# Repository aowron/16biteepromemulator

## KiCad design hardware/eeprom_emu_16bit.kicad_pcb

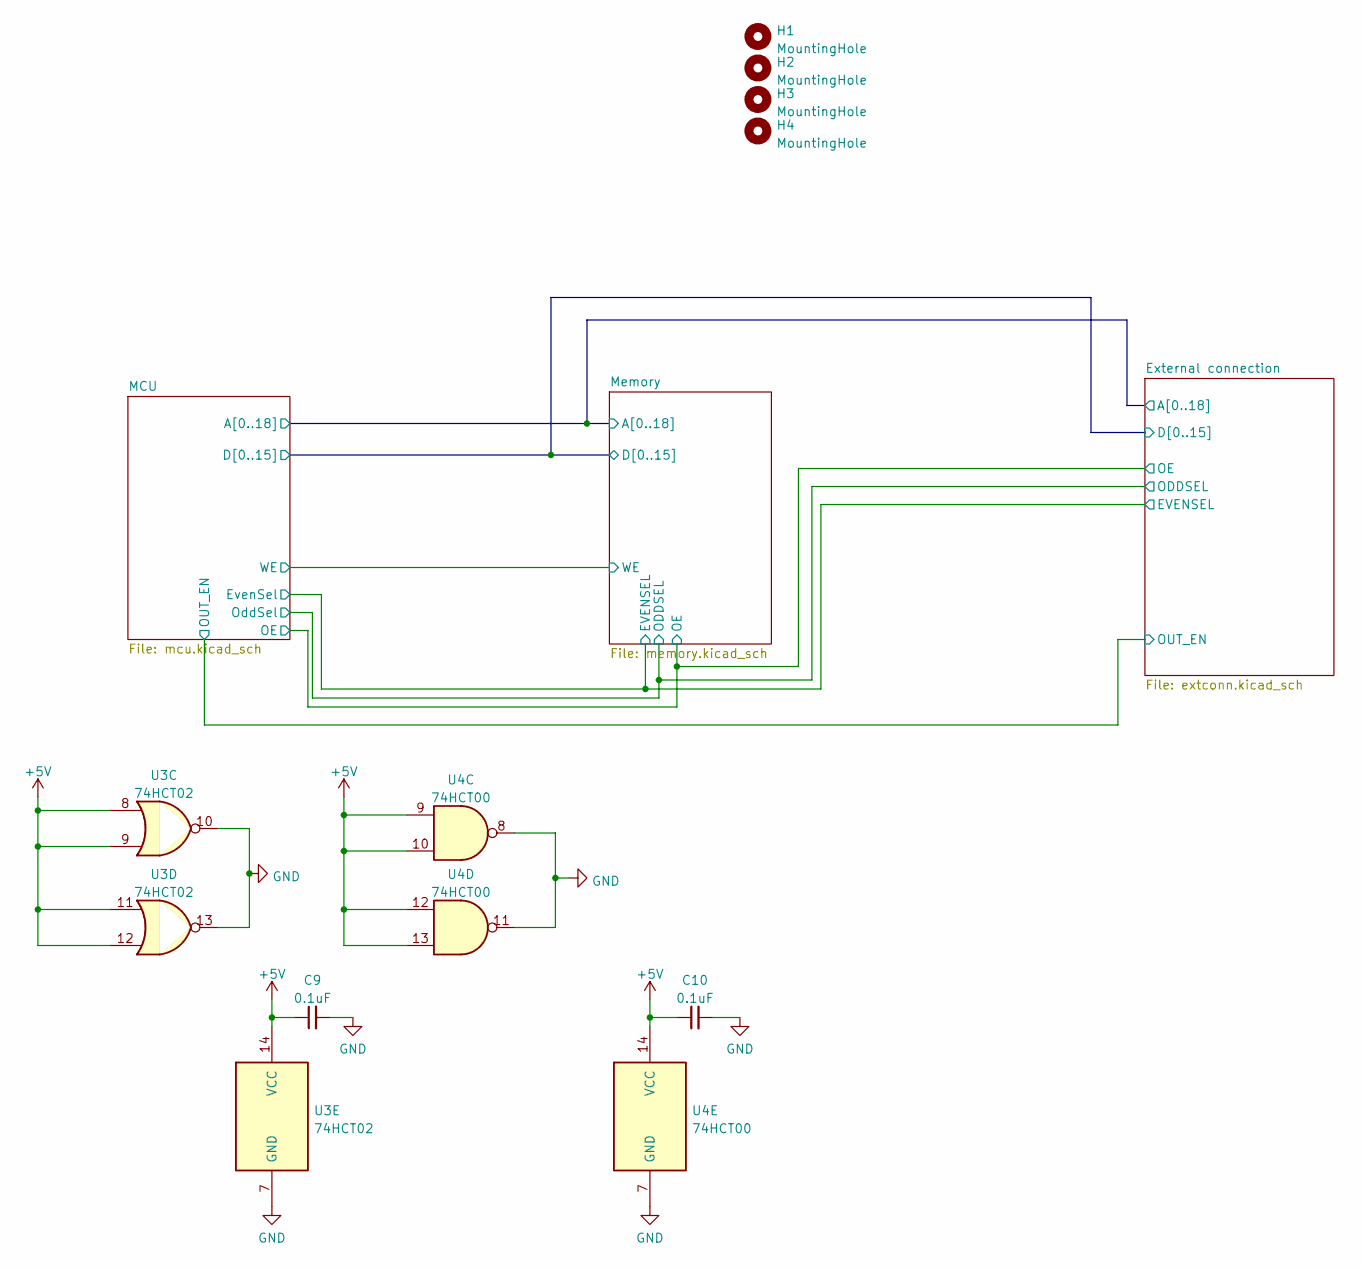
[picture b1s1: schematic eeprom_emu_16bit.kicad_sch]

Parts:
C9, C10: 0.1uF; C_1206_3216Metric_Pad1.33x1.80mm_HandSolder
H1, H2, H3, H4: MountingHole; MountingHole_3.2mm_M3_ISO7380_Pad
U3: 74HCT02; SOIC-14_3.9x8.7mm_P1.27mm
U4: 74HCT00; SOIC-14_3.9x8.7mm_P1.27mm

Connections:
+5V: C9.1, C10.1, U3.8, U3.9, U3.11, U3.12, U3.14 (VCC), U4.9, U4.10, U4.12, U4.13, U4.14 (VCC); also elsewhere on the board
GND: C9.2, C10.2, U3.7 (GND), U3.10, U3.13, U4.7 (GND), U4.8, U4.11; also elsewhere on the board

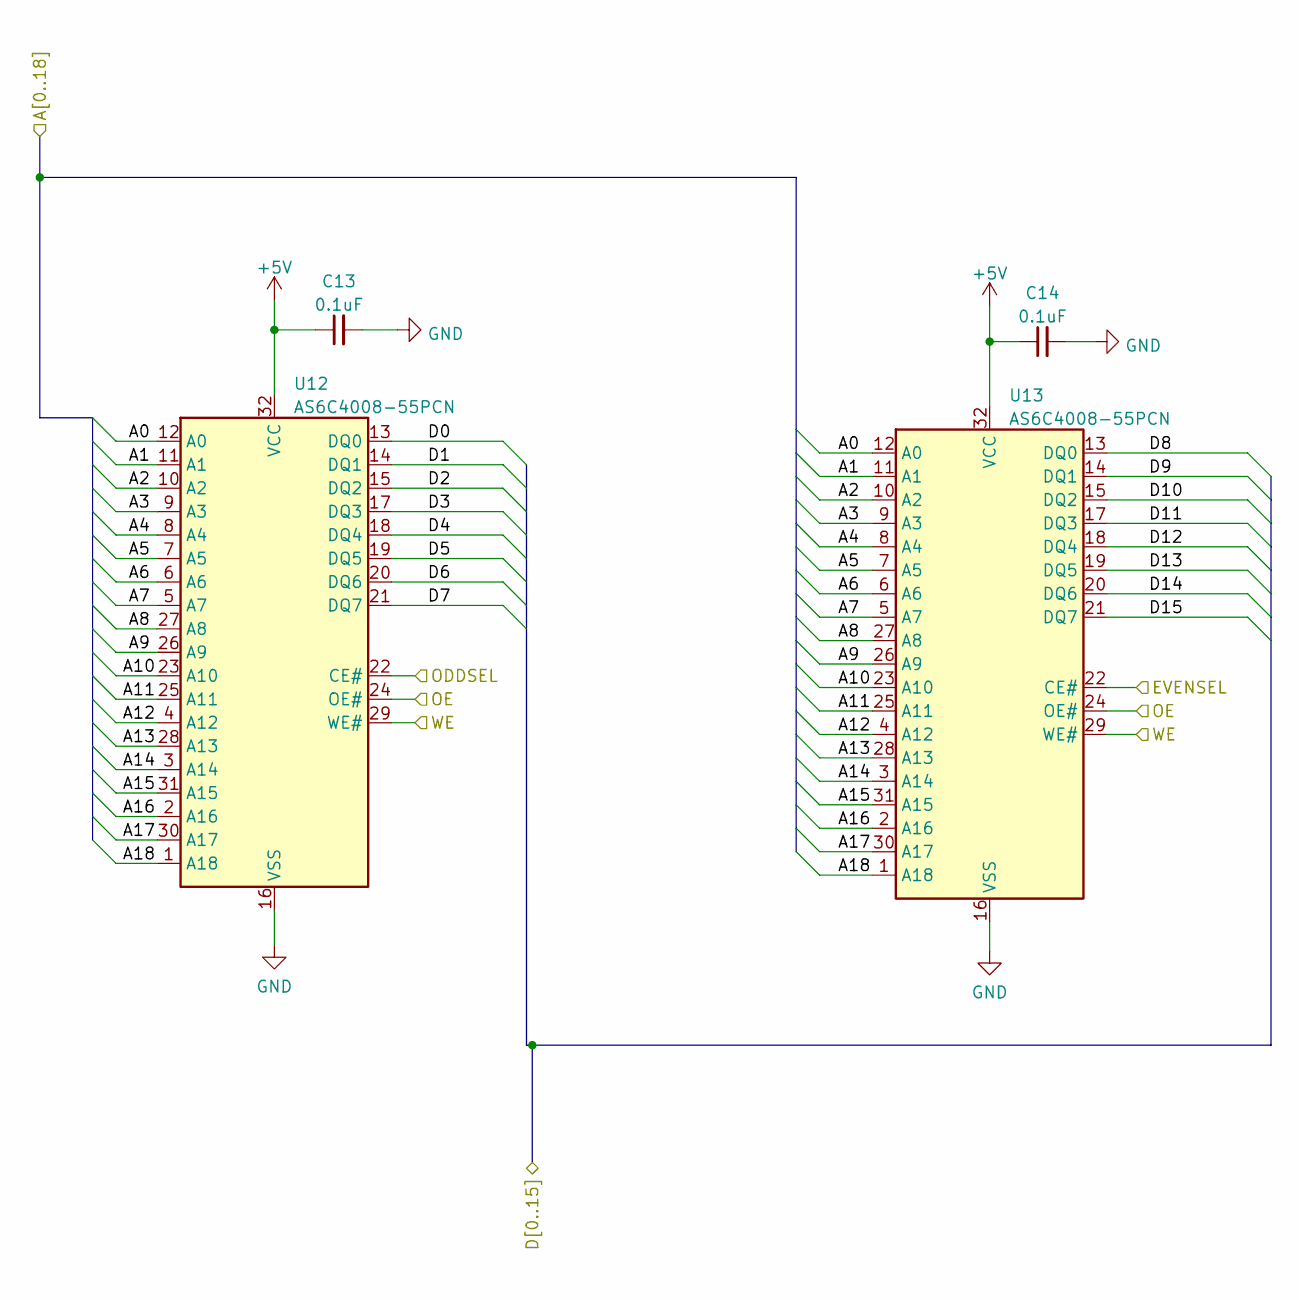
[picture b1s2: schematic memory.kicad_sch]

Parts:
C13, C14: 0.1uF; C_1206_3216Metric_Pad1.33x1.80mm_HandSolder
U12, U13: AS6C4008-55PCN; SSOP-32_11.305x20.495mm_P1.27mm

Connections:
+5V: C13.1, C14.1, U12.32 (VCC), U13.32 (VCC); also elsewhere on the board
/External connection/A0: U12.12 (A0), U13.12 (A0); also elsewhere on the board
/External connection/A1: U12.11 (A1), U13.11 (A1); also elsewhere on the board
/External connection/A2: U12.10 (A2), U13.10 (A2); also elsewhere on the board
/External connection/A3: U12.9 (A3), U13.9 (A3); also elsewhere on the board
/External connection/A4: U12.8 (A4), U13.8 (A4); also elsewhere on the board
/External connection/A5: U12.7 (A5), U13.7 (A5); also elsewhere on the board
/External connection/A6: U12.6 (A6), U13.6 (A6); also elsewhere on the board
/External connection/A7: U12.5 (A7), U13.5 (A7); also elsewhere on the board
/External connection/A8: U12.27 (A8), U13.27 (A8); also elsewhere on the board
/External connection/A9: U12.26 (A9), U13.26 (A9); also elsewhere on the board
/External connection/A10: U12.23 (A10), U13.23 (A10); also elsewhere on the board
/External connection/A11: U12.25 (A11), U13.25 (A11); also elsewhere on the board
/External connection/A12: U12.4 (A12), U13.4 (A12); also elsewhere on the board
/External connection/A13: U12.28 (A13), U13.28 (A13); also elsewhere on the board
/External connection/A14: U12.3 (A14), U13.3 (A14); also elsewhere on the board
/External connection/A15: U12.31 (A15), U13.31 (A15); also elsewhere on the board
/External connection/A16: U12.2 (A16), U13.2 (A16); also elsewhere on the board
/External connection/A17: U12.30 (A17), U13.30 (A17); also elsewhere on the board
/External connection/A18: U12.1 (A18), U13.1 (A18); also elsewhere on the board
/External connection/D0: U12.13 (DQ0); also elsewhere on the board
/External connection/D1: U12.14 (DQ1); also elsewhere on the board
/External connection/D2: U12.15 (DQ2); also elsewhere on the board
/External connection/D3: U12.17 (DQ3); also elsewhere on the board
/External connection/D4: U12.18 (DQ4); also elsewhere on the board
/External connection/D5: U12.19 (DQ5); also elsewhere on the board
/External connection/D6: U12.20 (DQ6); also elsewhere on the board
/External connection/D7: U12.21 (DQ7); also elsewhere on the board
/External connection/D8: U13.13 (DQ0); also elsewhere on the board
/External connection/D9: U13.14 (DQ1); also elsewhere on the board
/External connection/D10: U13.15 (DQ2); also elsewhere on the board
/External connection/D11: U13.17 (DQ3); also elsewhere on the board
/External connection/D12: U13.18 (DQ4); also elsewhere on the board
/External connection/D13: U13.19 (DQ5); also elsewhere on the board
/External connection/D14: U13.20 (DQ6); also elsewhere on the board
/External connection/D15: U13.21 (DQ7); also elsewhere on the board
/External connection/EVENSEL: U13.22 (CE#); also elsewhere on the board
/External connection/ODDSEL: U12.22 (CE#); also elsewhere on the board
/External connection/OE: U12.24 (OE#), U13.24 (OE#); also elsewhere on the board
/MCU/WE: U12.29 (WE#), U13.29 (WE#); also elsewhere on the board
GND: C13.2, C14.2, U12.16 (VSS), U13.16 (VSS); also elsewhere on the board

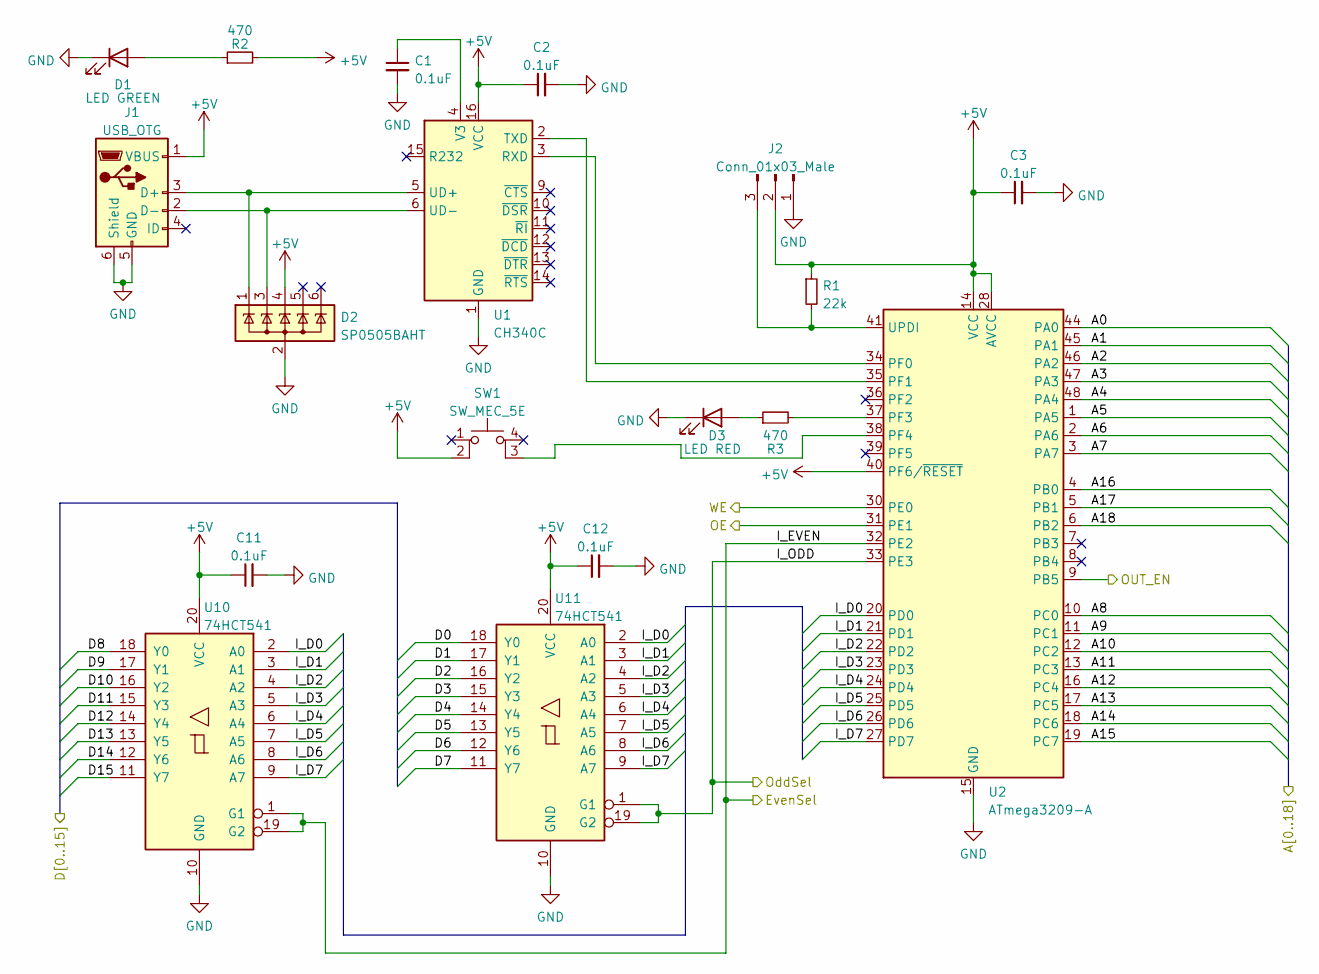
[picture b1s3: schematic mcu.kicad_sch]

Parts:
C1, C2, C3, C11, C12: 0.1uF; C_1206_3216Metric_Pad1.33x1.80mm_HandSolder
D1: LED GREEN; LED_0805_2012Metric_Pad1.15x1.40mm_HandSolder
D2: SP0505BAHT; SOT-23-6
D3: LED RED; LED_0805_2012Metric_Pad1.15x1.40mm_HandSolder
J1: USB_OTG; USB_Mini-B_Wuerth_65100516121_Horizontal
J2: Conn_01x03_Male; PinHeader_1x03_P2.54mm_Vertical
R1: 22k; R_0805_2012Metric_Pad1.20x1.40mm_HandSolder
R2, R3: 470; R_0805_2012Metric_Pad1.20x1.40mm_HandSolder
SW1: SW_MEC_5E; SW_PUSH_6mm_H4.3mm
U1: CH340C; SOIC-16_3.9x9.9mm_P1.27mm
U2: ATmega3209-A; TQFP-48_7x7mm_P0.5mm
U10, U11: 74HCT541; SOIC-20W_7.5x12.8mm_P1.27mm

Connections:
+5V: C2.1, C3.1, C11.1, C12.1, D2.4 (K), J1.1 (VBUS), J2.2, R1.1, R2.2, SW1.2, U1.16 (VCC), U2.14 (VCC), U2.28 (AVCC), U2.40 (PF6/~RESET), U2.42 (VCC), U10.20 (VCC), U11.20 (VCC); also elsewhere on the board
/External connection/A0: U2.44 (PA0); also elsewhere on the board
/External connection/A1: U2.45 (PA1); also elsewhere on the board
/External connection/A2: U2.46 (PA2); also elsewhere on the board
/External connection/A3: U2.47 (PA3); also elsewhere on the board
/External connection/A4: U2.48 (PA4); also elsewhere on the board
/External connection/A5: U2.1 (PA5); also elsewhere on the board
/External connection/A6: U2.2 (PA6); also elsewhere on the board
/External connection/A7: U2.3 (PA7); also elsewhere on the board
/External connection/A8: U2.10 (PC0); also elsewhere on the board
/External connection/A9: U2.11 (PC1); also elsewhere on the board
/External connection/A10: U2.12 (PC2); also elsewhere on the board
/External connection/A11: U2.13 (PC3); also elsewhere on the board
/External connection/A12: U2.16 (PC4); also elsewhere on the board
/External connection/A13: U2.17 (PC5); also elsewhere on the board
/External connection/A14: U2.18 (PC6); also elsewhere on the board
/External connection/A15: U2.19 (PC7); also elsewhere on the board
/External connection/A16: U2.4 (PB0); also elsewhere on the board
/External connection/A17: U2.5 (PB1); also elsewhere on the board
/External connection/A18: U2.6 (PB2); also elsewhere on the board
/External connection/D0: U11.18 (Y0); also elsewhere on the board
/External connection/D1: U11.17 (Y1); also elsewhere on the board
/External connection/D2: U11.16 (Y2); also elsewhere on the board
/External connection/D3: U11.15 (Y3); also elsewhere on the board
/External connection/D4: U11.14 (Y4); also elsewhere on the board
/External connection/D5: U11.13 (Y5); also elsewhere on the board
/External connection/D6: U11.12 (Y6); also elsewhere on the board
/External connection/D7: U11.11 (Y7); also elsewhere on the board
/External connection/D8: U10.18 (Y0); also elsewhere on the board
/External connection/D9: U10.17 (Y1); also elsewhere on the board
/External connection/D10: U10.16 (Y2); also elsewhere on the board
/External connection/D11: U10.15 (Y3); also elsewhere on the board
/External connection/D12: U10.14 (Y4); also elsewhere on the board
/External connection/D13: U10.13 (Y5); also elsewhere on the board
/External connection/D14: U10.12 (Y6); also elsewhere on the board
/External connection/D15: U10.11 (Y7); also elsewhere on the board
/External connection/EVENSEL: U2.32 (PE2), U10.1 (G1), U10.19 (G2); also elsewhere on the board
/External connection/ODDSEL: U2.33 (PE3), U11.1 (G1), U11.19 (G2); also elsewhere on the board
/External connection/OE: U2.31 (PE1); also elsewhere on the board
/External connection/OUT_EN: U2.9 (PB5); also elsewhere on the board
/MCU/I_D0: U2.20 (PD0), U10.2 (A0), U11.2 (A0)
/MCU/I_D1: U2.21 (PD1), U10.3 (A1), U11.3 (A1)
/MCU/I_D2: U2.22 (PD2), U10.4 (A2), U11.4 (A2)
/MCU/I_D3: U2.23 (PD3), U10.5 (A3), U11.5 (A3)
/MCU/I_D4: U2.24 (PD4), U10.6 (A4), U11.6 (A4)
/MCU/I_D5: U2.25 (PD5), U10.7 (A5), U11.7 (A5)
/MCU/I_D6: U2.26 (PD6), U10.8 (A6), U11.8 (A6)
/MCU/I_D7: U2.27 (PD7), U10.9 (A7), U11.9 (A7)
/MCU/WE: U2.30 (PE0); also elsewhere on the board
GND: C1.2, C2.2, C3.2, C11.2, C12.2, D1.1 (K), D2.2 (A), D3.1 (K), J1.5 (GND), J1.6 (Shield), J2.1, U1.1 (GND), U2.15 (GND), U2.29 (GND), U2.43 (GND), U10.10 (GND), U11.10 (GND); also elsewhere on the board
unnamed: C1.1, U1.4 (V3)
unnamed: D1.2 (A), R2.1
unnamed: D3.2 (A), R3.1
unnamed: D2.3 (K), J1.2 (D-), U1.6 (UD-)
unnamed: D2.1 (K), J1.3 (D+), U1.5 (UD+)
unnamed: J2.3, R1.2, U2.41 (UPDI)
unnamed: U1.2 (TXD), U2.35 (PF1)
unnamed: U1.3 (RXD), U2.34 (PF0)
unnamed: R3.2, U2.37 (PF3)
unnamed: SW1.3 (K), U2.38 (PF4)

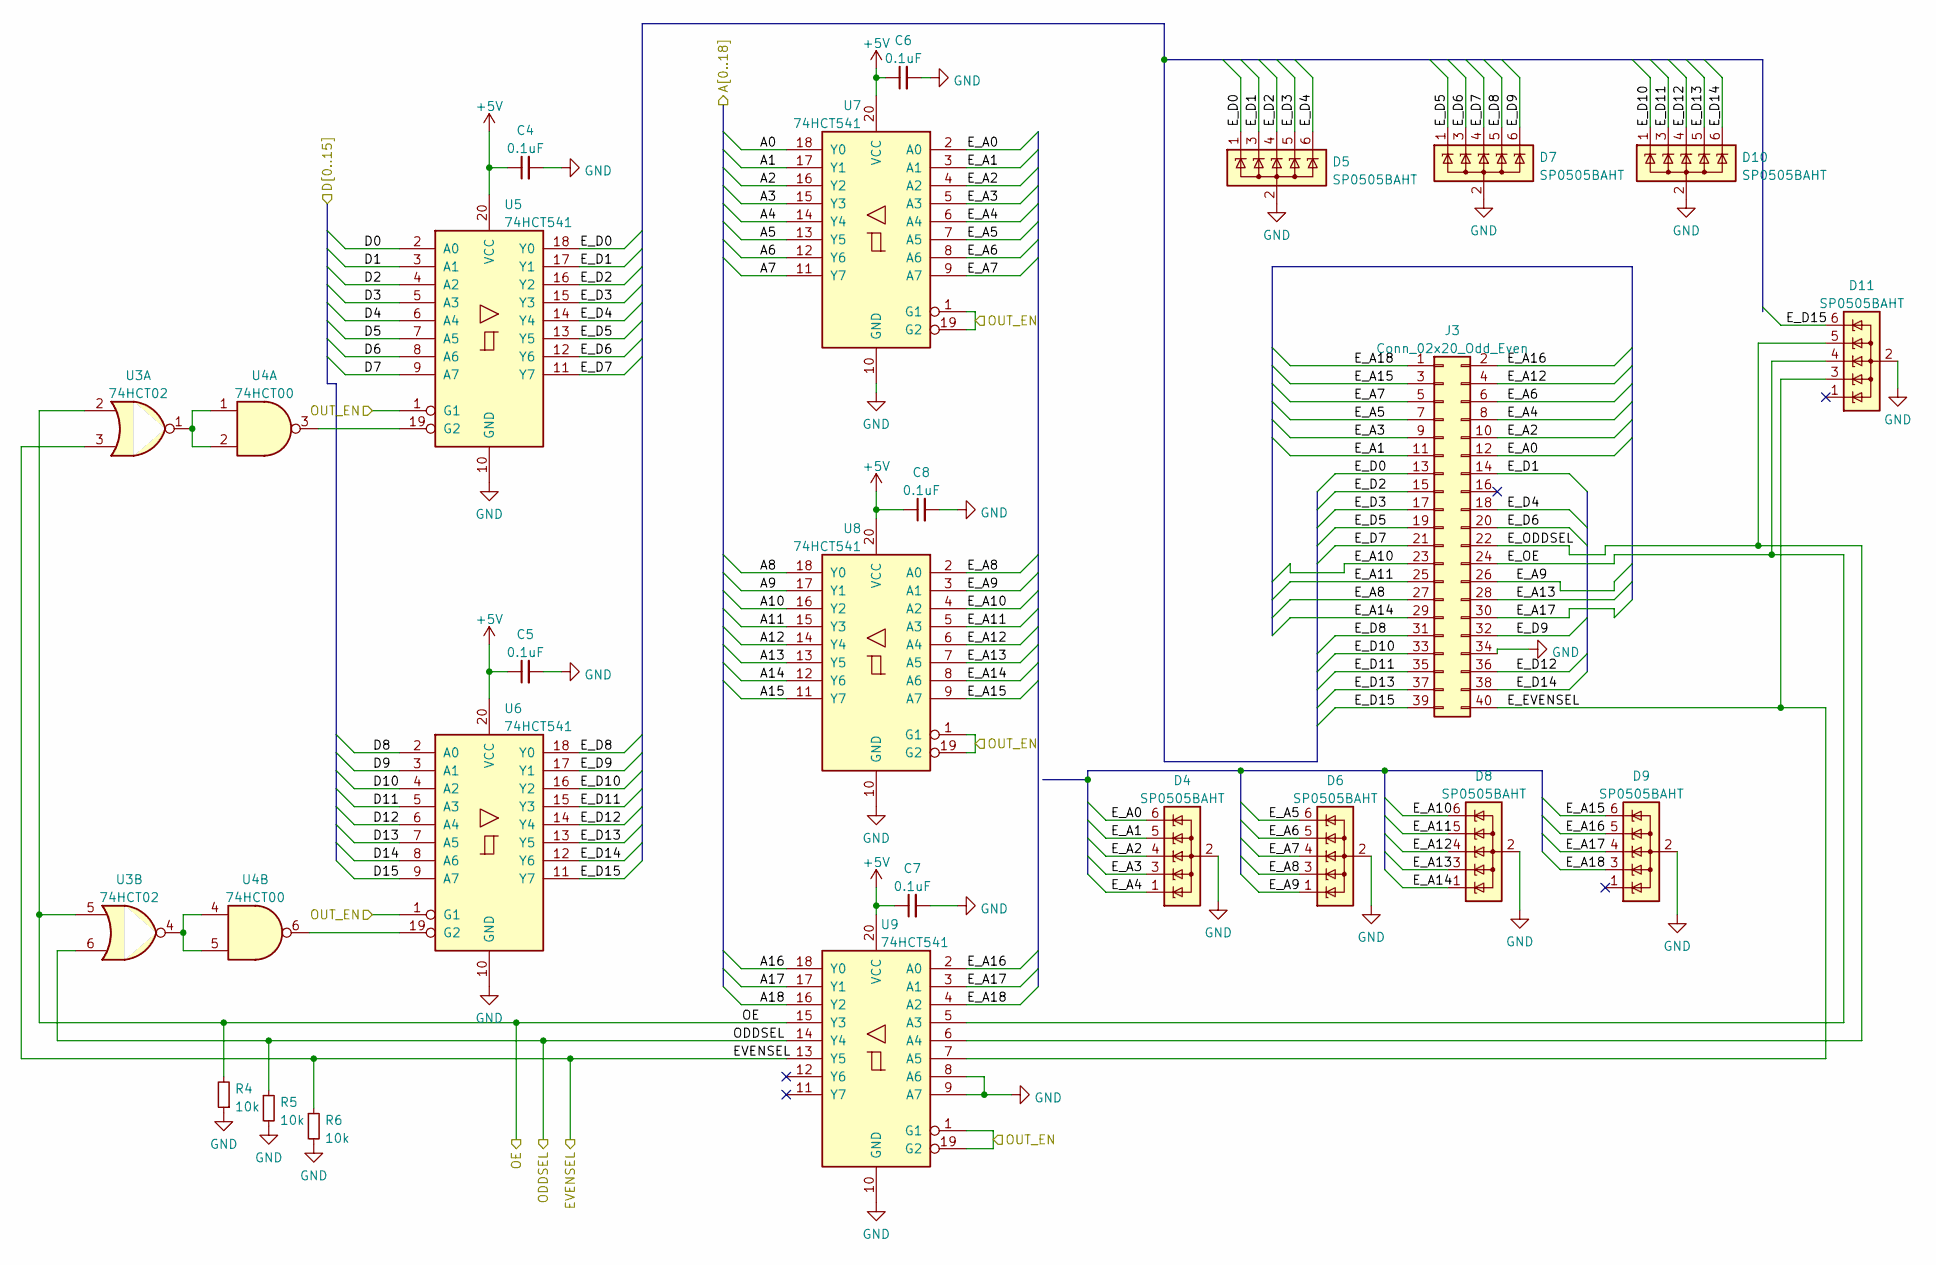
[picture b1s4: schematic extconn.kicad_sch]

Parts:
C4, C5, C6, C7, C8: 0.1uF; C_1206_3216Metric_Pad1.33x1.80mm_HandSolder
D4, D5, D6, D7, D8, D9, D10, D11: SP0505BAHT; SOT-23-6
J3: Conn_02x20_Odd_Even; IDC-Header_2x20_P2.54mm_Vertical
R4, R5, R6: 10k; R_0805_2012Metric_Pad1.20x1.40mm_HandSolder
U3: 74HCT02; SOIC-14_3.9x8.7mm_P1.27mm
U4: 74HCT00; SOIC-14_3.9x8.7mm_P1.27mm
U5, U6, U7, U8, U9: 74HCT541; SOIC-20W_7.5x12.8mm_P1.27mm

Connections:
+5V: C4.1, C5.1, C6.1, C7.1, C8.1, U5.20 (VCC), U6.20 (VCC), U7.20 (VCC), U8.20 (VCC), U9.20 (VCC); also elsewhere on the board
/External connection/A0: U7.18 (Y0); also elsewhere on the board
/External connection/A1: U7.17 (Y1); also elsewhere on the board
/External connection/A2: U7.16 (Y2); also elsewhere on the board
/External connection/A3: U7.15 (Y3); also elsewhere on the board
/External connection/A4: U7.14 (Y4); also elsewhere on the board
/External connection/A5: U7.13 (Y5); also elsewhere on the board
/External connection/A6: U7.12 (Y6); also elsewhere on the board
/External connection/A7: U7.11 (Y7); also elsewhere on the board
/External connection/A8: U8.18 (Y0); also elsewhere on the board
/External connection/A9: U8.17 (Y1); also elsewhere on the board
/External connection/A10: U8.16 (Y2); also elsewhere on the board
/External connection/A11: U8.15 (Y3); also elsewhere on the board
/External connection/A12: U8.14 (Y4); also elsewhere on the board
/External connection/A13: U8.13 (Y5); also elsewhere on the board
/External connection/A14: U8.12 (Y6); also elsewhere on the board
/External connection/A15: U8.11 (Y7); also elsewhere on the board
/External connection/A16: U9.18 (Y0); also elsewhere on the board
/External connection/A17: U9.17 (Y1); also elsewhere on the board
/External connection/A18: U9.16 (Y2); also elsewhere on the board
/External connection/D0: U5.2 (A0); also elsewhere on the board
/External connection/D1: U5.3 (A1); also elsewhere on the board
/External connection/D2: U5.4 (A2); also elsewhere on the board
/External connection/D3: U5.5 (A3); also elsewhere on the board
/External connection/D4: U5.6 (A4); also elsewhere on the board
/External connection/D5: U5.7 (A5); also elsewhere on the board
/External connection/D6: U5.8 (A6); also elsewhere on the board
/External connection/D7: U5.9 (A7); also elsewhere on the board
/External connection/D8: U6.2 (A0); also elsewhere on the board
/External connection/D9: U6.3 (A1); also elsewhere on the board
/External connection/D10: U6.4 (A2); also elsewhere on the board
/External connection/D11: U6.5 (A3); also elsewhere on the board
/External connection/D12: U6.6 (A4); also elsewhere on the board
/External connection/D13: U6.7 (A5); also elsewhere on the board
/External connection/D14: U6.8 (A6); also elsewhere on the board
/External connection/D15: U6.9 (A7); also elsewhere on the board
/External connection/EVENSEL: R6.1, U3.3, U9.13 (Y5); also elsewhere on the board
/External connection/E_A0: D4.6 (K), J3.12, U7.2 (A0)
/External connection/E_A1: D4.5 (K), J3.11, U7.3 (A1)
/External connection/E_A2: D4.4 (K), J3.10, U7.4 (A2)
/External connection/E_A3: D4.3 (K), J3.9, U7.5 (A3)
/External connection/E_A4: D4.1 (K), J3.8, U7.6 (A4)
/External connection/E_A5: D6.6 (K), J3.7, U7.7 (A5)
/External connection/E_A6: D6.5 (K), J3.6, U7.8 (A6)
/External connection/E_A7: D6.4 (K), J3.5, U7.9 (A7)
/External connection/E_A8: D6.3 (K), J3.27, U8.2 (A0)
/External connection/E_A9: D6.1 (K), J3.26, U8.3 (A1)
/External connection/E_A10: D8.6 (K), J3.23, U8.4 (A2)
/External connection/E_A11: D8.5 (K), J3.25, U8.5 (A3)
/External connection/E_A12: D8.4 (K), J3.4, U8.6 (A4)
/External connection/E_A13: D8.3 (K), J3.28, U8.7 (A5)
/External connection/E_A14: D8.1 (K), J3.29, U8.8 (A6)
/External connection/E_A15: D9.6 (K), J3.3, U8.9 (A7)
/External connection/E_A16: D9.5 (K), J3.2, U9.2 (A0)
/External connection/E_A17: D9.4 (K), J3.30, U9.3 (A1)
/External connection/E_A18: D9.3 (K), J3.1, U9.4 (A2)
/External connection/E_D0: D5.1 (K), J3.13, U5.18 (Y0)
/External connection/E_D1: D5.3 (K), J3.14, U5.17 (Y1)
/External connection/E_D2: D5.4 (K), J3.15, U5.16 (Y2)
/External connection/E_D3: D5.5 (K), J3.17, U5.15 (Y3)
/External connection/E_D4: D5.6 (K), J3.18, U5.14 (Y4)
/External connection/E_D5: D7.1 (K), J3.19, U5.13 (Y5)
/External connection/E_D6: D7.3 (K), J3.20, U5.12 (Y6)
/External connection/E_D7: D7.4 (K), J3.21, U5.11 (Y7)
/External connection/E_D8: D7.5 (K), J3.31, U6.18 (Y0)
/External connection/E_D9: D7.6 (K), J3.32, U6.17 (Y1)
/External connection/E_D10: D10.1 (K), J3.33, U6.16 (Y2)
/External connection/E_D11: D10.3 (K), J3.35, U6.15 (Y3)
/External connection/E_D12: D10.4 (K), J3.36, U6.14 (Y4)
/External connection/E_D13: D10.5 (K), J3.37, U6.13 (Y5)
/External connection/E_D14: D10.6 (K), J3.38, U6.12 (Y6)
/External connection/E_D15: D11.6 (K), J3.39, U6.11 (Y7)
/External connection/E_EVENSEL: D11.3 (K), J3.40, U9.7 (A5)
/External connection/E_ODDSEL: D11.5 (K), J3.22, U9.6 (A4)
/External connection/E_OE: D11.4 (K), J3.24, U9.5 (A3)
/External connection/ODDSEL: R5.1, U3.6, U9.14 (Y4); also elsewhere on the board
/External connection/OE: R4.2, U3.2, U3.5, U9.15 (Y3); also elsewhere on the board
/External connection/OUT_EN: U5.1 (G1), U6.1 (G1), U7.1 (G1), U7.19 (G2), U8.1 (G1), U8.19 (G2), U9.1 (G1), U9.19 (G2); also elsewhere on the board
GND: C4.2, C5.2, C6.2, C7.2, C8.2, D4.2 (A), D5.2 (A), D6.2 (A), D7.2 (A), D8.2 (A), D9.2 (A), D10.2 (A), D11.2 (A), J3.34, R4.1, R5.2, R6.2, U5.10 (GND), U6.10 (GND), U7.10 (GND), U8.10 (GND), U9.8 (A6), U9.9 (A7), U9.10 (GND); also elsewhere on the board
unnamed: U3.1, U4.1, U4.2
unnamed: U3.4, U4.4, U4.5
unnamed: U4.3, U5.19 (G2)
unnamed: U4.6, U6.19 (G2)

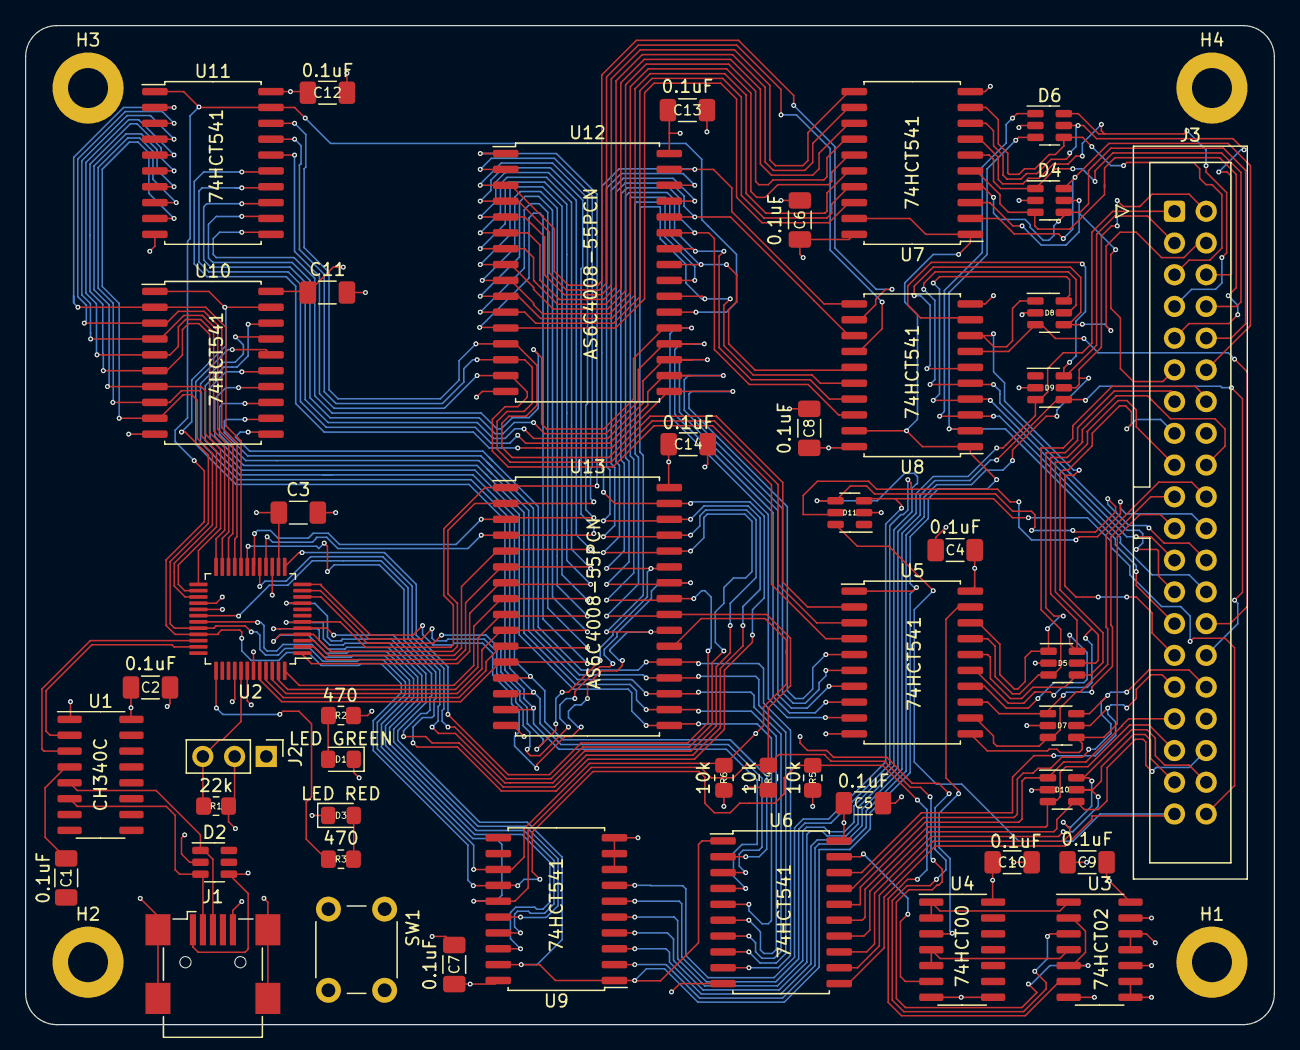
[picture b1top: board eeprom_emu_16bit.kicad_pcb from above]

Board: 4 copper layers, 100.0 x 80.0 mm, 52 parts (0 on the bottom side), 101 nets.

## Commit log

2022-09-04 Initial commit: Schematic design
2022-09-10 Hardware: Drew up the rest of the pcb
